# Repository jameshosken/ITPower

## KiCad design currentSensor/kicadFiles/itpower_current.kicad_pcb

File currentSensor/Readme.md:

# Current Sensor

We are building an energy monitoring system at ITP. 

TLDR: A current sensor with a precision rectifier circuit connected to an arduino gives us the current readings - we are monitoring our energy consumption and habits. 

Read about how the project evolved over time on the blog 
https://itp.nyu.edu/classes/itpower/2017/01/04/phase-i-process-learning/

Phase II 
https://itp.nyu.edu/classes/itpower/2017/05/04/facilities/

Current Sensor 
https://itp.nyu.edu/classes/itpower/2018/02/09/current-sensor/

Rectifier circuit 
https://itp.nyu.edu/classes/itpower/2018/03/04/rectifier-circuit/
https://itp.nyu.edu/classes/itpower/2018/03/08/testing-rectifier-circuit-on-current-sensor/
https://itp.nyu.edu/classes/itpower/2018/03/13/simplified-rectifier-circuit-on-perfboard/
https://itp.nyu.edu/classes/itpower/2018/03/27/precision-rectifier-circuit-on-perf-board/

Reference links 

https://learn.openenergymonitor.org/electricity-monitoring/ctac/calibration

https://www.arduino.cc/reference/en/language/functions/analog-io/analogreference/

https://itp.nyu.edu/classes/itpower/2018/02/09/current-sensor/

https://itp.nyu.edu/classes/itpower/2018/03/04/rectifier-circuit/

https://www.crmagnetics.com/Assets/ProductPDFs/Precision%20Rectifier%20Circuit%20for%20CT%20Signal%20Conditioning.pdf

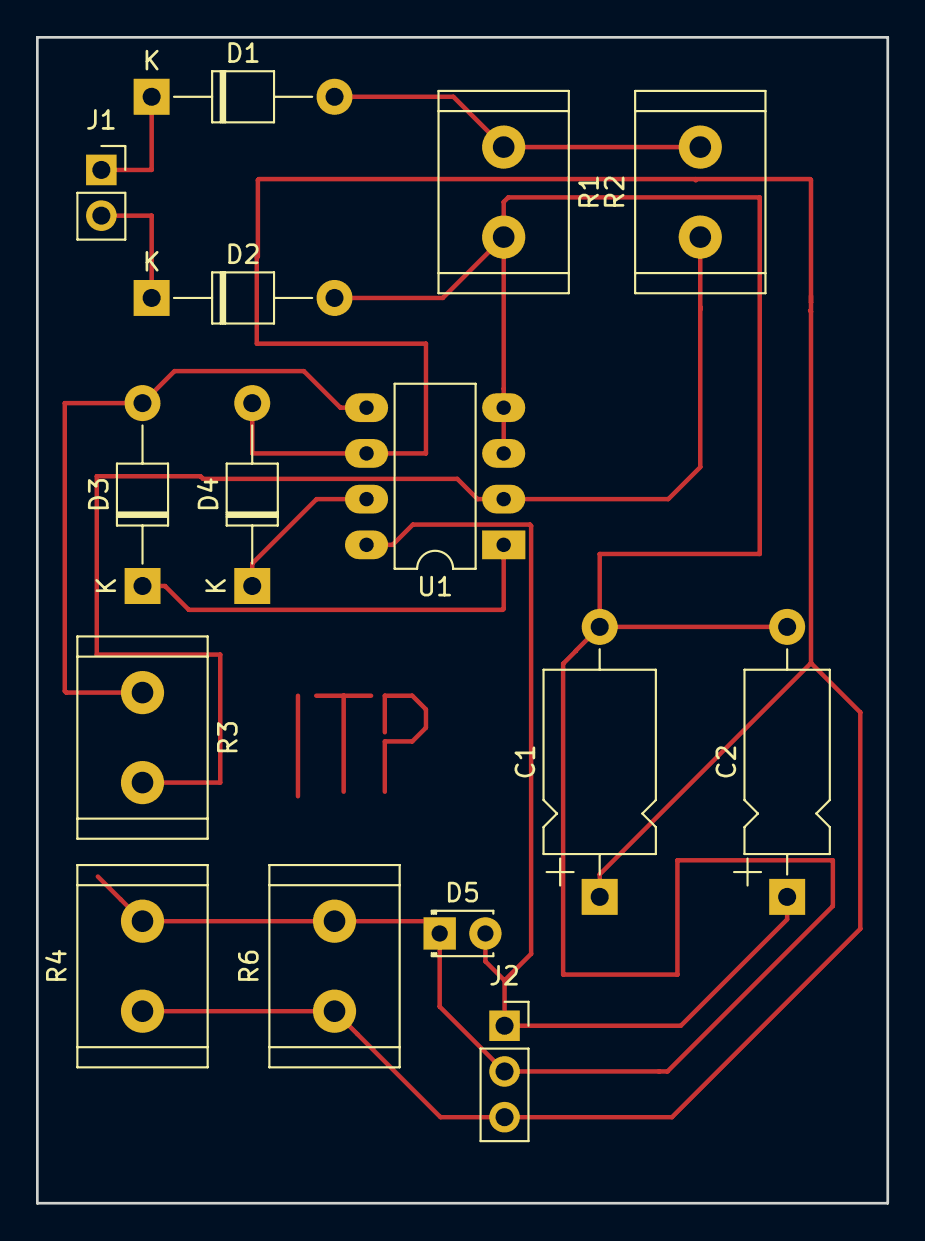
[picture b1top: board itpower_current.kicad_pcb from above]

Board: 2 copper layers, 47.2 x 64.8 mm, 15 parts (0 on the bottom side), 10 nets.

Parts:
C1: 47uF; CP_Axial_L10.0mm_D6.0mm_P15.00mm_Horizontal
C2: 100nF; CP_Axial_L10.0mm_D4.5mm_P15.00mm_Horizontal
D1, D2, D3, D4: DIODE; D_T-1_P10.16mm_Horizontal
D5: LED; LED_D1.8mm_W3.3mm_H2.4mm
J1: Conn_01x02_Male; PinSocket_1x02_P2.54mm_Vertical
J2: Conn_01x03_Male; PinSocket_1x03_P2.54mm_Vertical
R1: 68 ohms; R_Radial_Power_L11.0mm_W7.0mm_P5.00mm
R2, R3: 680 ohms; R_Radial_Power_L11.0mm_W7.0mm_P5.00mm
R4: 10k; R_Radial_Power_L11.0mm_W7.0mm_P5.00mm
R6: 3.3k; R_Radial_Power_L11.0mm_W7.0mm_P5.00mm
U1: LM358; DIP-8_W7.62mm_LongPads

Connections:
+5V: C2.1, D5.2, J2.1, U1.8
GND: C1.2, C2.2, D2.2, D5.1, J2.2, R1.2, R4.2, R6.2, U1.3, U1.4
unnamed: C1.1, D4.2, J2.3, R4.1, R6.1, U1.6
unnamed: D1.1, J1.1
unnamed: D1.2, R1.1, R2.2
unnamed: D2.1, J1.2
unnamed: D3.1, U1.1
unnamed: D3.2, R3.1, U1.5
unnamed: D4.1, U1.7
unnamed: R2.1, R3.2, U1.2

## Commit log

2017-06-13 added express
2017-06-13 added comment to code
2018-01-17 edit SQL query
2018-03-07 current sensor code
2018-03-07 edited
2018-03-07 added readme
2018-10-29 added old solar monitor scripts
2018-12-10 adding KiCAD files
2018-12-10 edited readme
2019-02-26 Add setup guide and documentation
2019-02-26 Add example for wind and rain
